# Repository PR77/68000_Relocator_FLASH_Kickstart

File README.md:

# 68000 Relocator with FLASH based Kickstart
Forked from https://github.com/AwesomeInferno/68000Relocator and modified to support FLASH Kickstart allowing programming in system.

# Warning
This design has not been compliance tested and will not be. It may cause damage to your A500. I take no responsibility for this. I accept no responsibility for any damage to any equipment that results from the use of this design and its components. IT IS ENTIRELY AT YOUR OWN RISK!

# Overview
To allow for Flash Kickstart images to be mapped in the same address space as existing ROM Kickstart without the need to remove the existing ROM. This design is targeting an accelerated A500(+) system which also require a CPU relocation.

### Appearance
Nice 3D model:

... this is the final design.

### Prototype
Drawing in from the experience and usefulness of my prototyping jig created for my Rev-1 Accelerator (https://github.com/PR77/A500_ACCEL_RAM_IDE-Rev-1), I decided to do the same for this hardware expansion.

So the prototype looks like this:

To keep the prototype simple, instead of using Flash devices (AMD AM29F040B are my target has I have these and experience with the devices) I used simple SRAMs (also from my Accelerator). There was also the learning curve with using VBCC (http://eab.abime.net/showthread.php?t=83113) to develop the software to control the hardware, but with that sorted out I managed to finally get the prototype to work.

### Final Hardware
Here is the final hardware loaded and installed with my Rev-2 Accelerator (https://github.com/PR77/A500_ACCEL_RAM_IDE-Rev-2). I was not able to easily source new AMD AM29F040B Flash devices so I changed over to SST39SF0x0A devices. They are JEDEC compliant so no issue with the pinout. Just watch out for the device identification in the SW.

### BOM
For those wanting to build their own hardware, here is the BOM;

| Reference(s) | Value      | Footprint                                                      |
|--------------|------------|----------------------------------------------------------------|
| C1           | 10uF       | Capacitors_Tantalum_SMD:CP_Tantalum_Case-B_EIA-3528-21_Hand    |
| C2           | 10uF       | Capacitors_Tantalum_SMD:CP_Tantalum_Case-B_EIA-3528-21_Hand    |
| C3           | 100nF      | Capacitors_SMD:C_0805_HandSoldering                            |
| C4           | 100nF      | Capacitors_SMD:C_0805_HandSoldering                            |
| C5           | 100nF      | Capacitors_SMD:C_0805_HandSoldering                            |
| C6           | 100nF      | Capacitors_SMD:C_0805_HandSoldering                            |
| J3           | BLOCK      | Pin_Headers:Pin_Header_Straight_1x02_Pitch2.54mm               |
| J4           | JTAG       | Pin_Headers:Pin_Header_Straight_1x06_Pitch2.54mm               |
| R1           | 10K        | Resistors_SMD:R_0805_HandSoldering                             |
| R2           | 10K        | Resistors_SMD:R_0805_HandSoldering                             |
| R3           | 10K        | Resistors_SMD:R_0805_HandSoldering                             |
| U1           | 68000D     | Pin_Headers:Pin_Header_Straight_2x32_Pitch2.54mm               |
| U2           | 68000D     | Housings_DIP:DIP-64_W22.86mm_Socket_LongPads                   |
| U3           | SST39SF040 | Housings_DIP:DIP-32_W15.24mm_Socket                            |
| U4           | SST39SF040 | Housings_DIP:DIP-32_W15.24mm_Socket                            |
| U5           | XC9572VQ44 | Housings_QFP:TQFP-44_10x10mm_Pitch0.8mm                        |
| U6           | LM1117-3.3 | TO_SOT_Packages_SMD:SOT-223-3_TabPin2                          |

### In Operation
My test Amiga 500 has a ROM Kickstart version 1.2, so the boot screen looks like this:

Then when loading into RAM Kickstart version 3.1 the software will make a simple dump of the RAM to the console to ensure it has been written correctly (data blurred to avoid any potential (C) issues). Essentially some basic debugging which looks like this:

... so now, using the magic sequence, I have Kickstart version 3.1 as shown here:

### How It Works
In principle the operation is fairly simple. A CPLD is used to switch between the ROM Kickstart on the Motherboard or the Flash Kickstart on the CPU Relocator. Switching is performed by an active /RESET (CTRL-A-A) without interruption for longer than 1 second. Shorter /RESET durations will simply just reset the Amiga. After a POR (Power On Reset) by default the Flash Kickstart on the CPU Relocator will be used.

#### ROM based Kickstart
When ROM Kickstart is being used, the hardware simply passed /AS to the Amiga Motherboard to allow GARY perform the address decode and chip select of the internal ROM. During this process, the Flash Kickstart is simply not used - except when programming. A Zorro II space of 512K is  requested and allocated by the Amiga which maps to the Flash devices.

When programming the Flash devices, access is via this Zorro II space. Programming of the Flash devices can only be performed when ROM Kickstart is being used.

#### FLASH based Kickstart
When Flash Kickstart is being used, the hardware simply blocks /AS to the Amiga Motherboard and the CPLD will perform the operation of Flash device control. As /AS is not asserted on the Amiga Motherboard, and therefore no GARY decode, the Relocator CPLD will then also assert the /DTACK after placing data on the bus - this is needed to complete the CPU cycle.

Flash Kickstarts will always be visible from base address 0xF80000. This means, if 256K images would be used, then it will need to be duplicated to populate the entire 512K region size. This is to ensure the correct SP and IP initisation (see Overlay Interception). 256K images generally start from address 0xFC0000 (as opposed to 0xF80000).

#### Overlay Interception
When Flash Kickstart mode is being used, the CPLD will also intercept the overlay of the Kickstart in the 0x000000 memory space until the first access to the custom chip register is performed. This ensures the correct SP and IP initialisation is performed directly after POR (Power On Reset) as the Flash Kickstart is used by default.

### Known Issues And Pending Items
The following items are pending:

1. Will update the software to not load the entire Kickstart content into RAM before programming; rather will load 64K chunks at a time.
2. Support for ROMs based at address 0xF00000.

### External Contributions
Thanks to the Open Source efforts, here is a list of improvements people have made:

1. Side Slot expander version and GUI - https://github.com/KaiEmilW/A500-Side-Expansion-Slot-CPU-Relocator

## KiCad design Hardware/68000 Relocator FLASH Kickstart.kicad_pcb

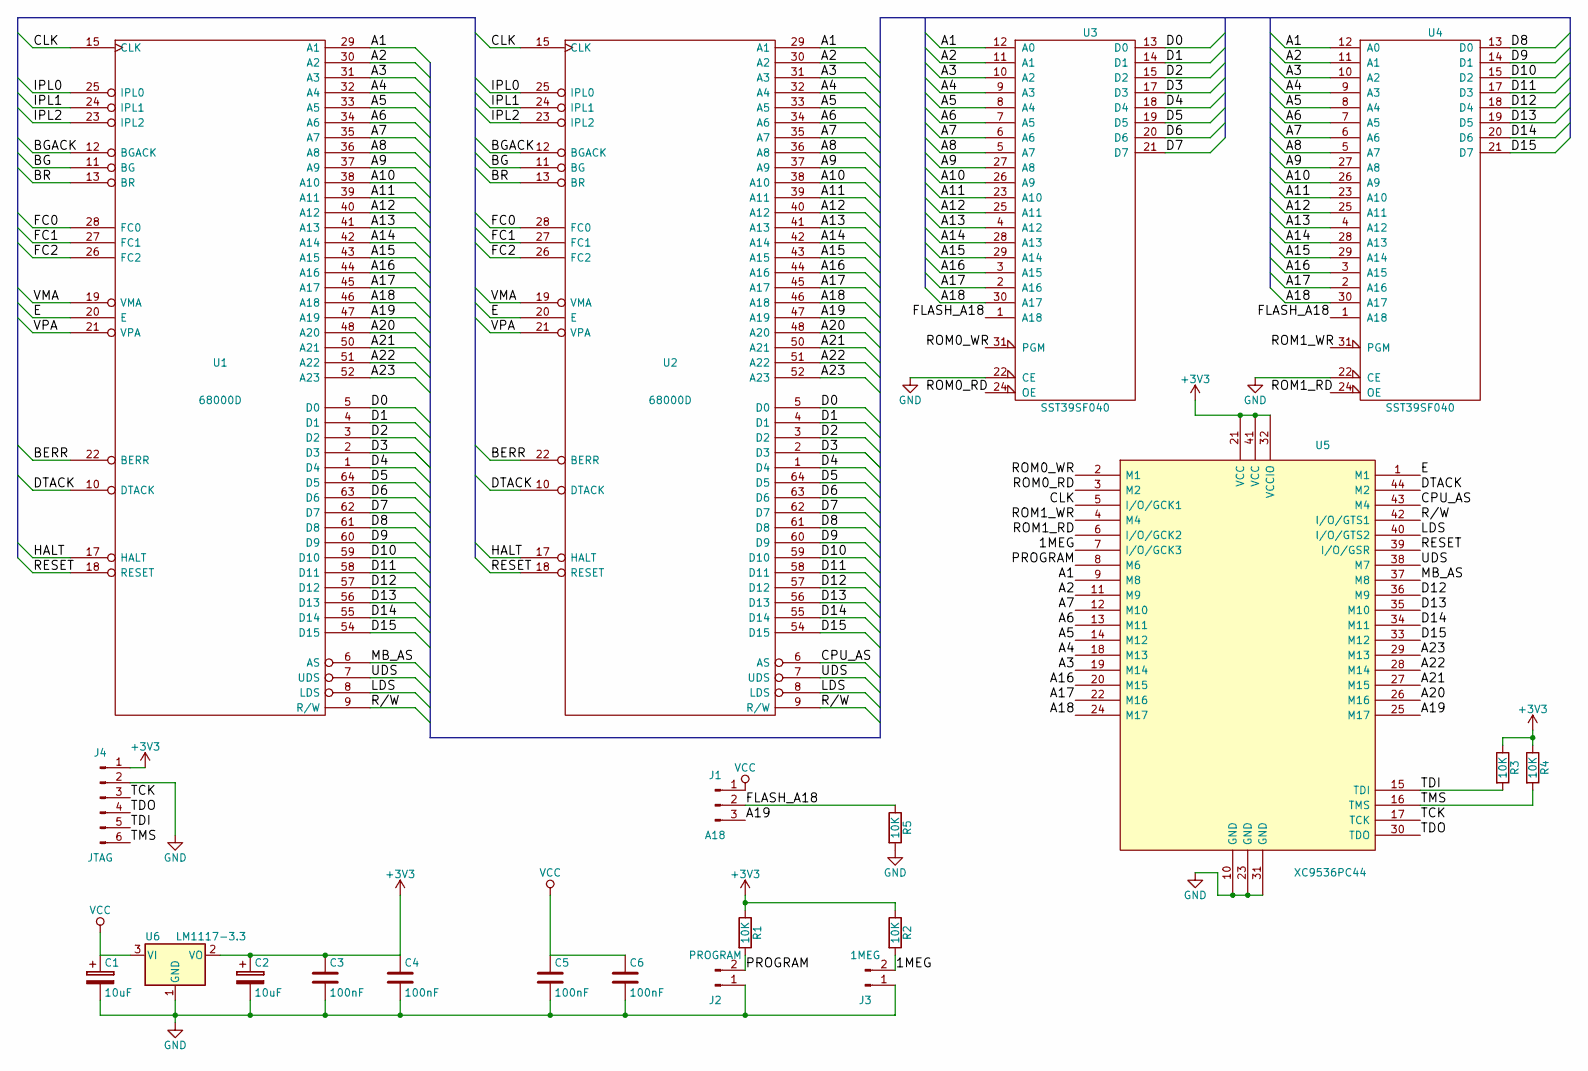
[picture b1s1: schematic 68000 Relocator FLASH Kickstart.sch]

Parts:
C1, C2: 10uF; CP_Tantalum_Case-B_EIA-3528-21_Hand
C3, C4, C5, C6: 100nF; C_0805_HandSoldering
J1: A18; Pin_Header_Straight_1x03_Pitch2.54mm
J2: PROGRAM; Pin_Header_Straight_1x02_Pitch2.54mm
J3: 1MEG; Pin_Header_Straight_1x02_Pitch2.54mm
J4: JTAG; Pin_Header_Straight_1x06_Pitch2.54mm
R1, R2, R3, R4, R5: 10K; R_0805_HandSoldering
U1, U2: 68000D; DIP-64_W22.86mm_Socket_LongPads
U3, U4: SST39SF040; PLCC-32
U5: XC9536PC44; TQFP-44_10x10mm_Pitch0.8mm
U6: LM1117-3.3; SOT-223-3_TabPin2

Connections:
+3V3: C2.1, C3.1, C4.1, J4.1, R1.1, R2.1, R3.1, R4.1, U5.21 (VCC), U5.32 (VCCIO), U5.41 (VCC), U6.2 (VO)
/1MEG: J3.2, R2.2, U5.7 (I/O/GCK3)
/A1: U1.29 (A1), U2.29 (A1), U3.12 (A0), U4.12 (A0), U5.9 (M8)
/A2: U1.30 (A2), U2.30 (A2), U3.11 (A1), U4.11 (A1), U5.11 (M9)
/A3: U1.31 (A3), U2.31 (A3), U3.10 (A2), U4.10 (A2), U5.19 (M14)
/A4: U1.32 (A4), U2.32 (A4), U3.9 (A3), U4.9 (A3), U5.18 (M13)
/A5: U1.33 (A5), U2.33 (A5), U3.8 (A4), U4.8 (A4), U5.14 (M12)
/A6: U1.34 (A6), U2.34 (A6), U3.7 (A5), U4.7 (A5), U5.13 (M11)
/A7: U1.35 (A7), U2.35 (A7), U3.6 (A6), U4.6 (A6), U5.12 (M10)
/A8: U1.36 (A8), U2.36 (A8), U3.5 (A7), U4.5 (A7)
/A9: U1.37 (A9), U2.37 (A9), U3.27 (A8), U4.27 (A8)
/A10: U1.38 (A10), U2.38 (A10), U3.26 (A9), U4.26 (A9)
/A11: U1.39 (A11), U2.39 (A11), U3.23 (A10), U4.23 (A10)
/A12: U1.40 (A12), U2.40 (A12), U3.25 (A11), U4.25 (A11)
/A13: U1.41 (A13), U2.41 (A13), U3.4 (A12), U4.4 (A12)
/A14: U1.42 (A14), U2.42 (A14), U3.28 (A13), U4.28 (A13)
/A15: U1.43 (A15), U2.43 (A15), U3.29 (A14), U4.29 (A14)
/A16: U1.44 (A16), U2.44 (A16), U3.3 (A15), U4.3 (A15), U5.20 (M15)
/A17: U1.45 (A17), U2.45 (A17), U3.2 (A16), U4.2 (A16), U5.22 (M16)
/A18: U1.46 (A18), U2.46 (A18), U3.30 (A17), U4.30 (A17), U5.24 (M17)
/A19: J1.3, U1.47 (A19), U2.47 (A19), U5.25 (M17)
/A20: U1.48 (A20), U2.48 (A20), U5.26 (M16)
/A21: U1.50 (A21), U2.50 (A21), U5.27 (M15)
/A22: U1.51 (A22), U2.51 (A22), U5.28 (M14)
/A23: U1.52 (A23), U2.52 (A23), U5.29 (M13)
/BERR: U1.22 (BERR), U2.22 (BERR)
/BG: U1.11 (BG), U2.11 (BG)
/BGACK: U1.12 (BGACK), U2.12 (BGACK)
/BR: U1.13 (BR), U2.13 (BR)
/CLK: U1.15 (CLK), U2.15 (CLK), U5.5 (I/O/GCK1)
/CPU_AS: U2.6 (AS), U5.43 (M4)
/D0: U1.5 (D0), U2.5 (D0), U3.13 (D0)
/D1: U1.4 (D1), U2.4 (D1), U3.14 (D1)
/D2: U1.3 (D2), U2.3 (D2), U3.15 (D2)
/D3: U1.2 (D3), U2.2 (D3), U3.17 (D3)
/D4: U1.1 (D4), U2.1 (D4), U3.18 (D4)
/D5: U1.64 (D5), U2.64 (D5), U3.19 (D5)
/D6: U1.63 (D6), U2.63 (D6), U3.20 (D6)
/D7: U1.62 (D7), U2.62 (D7), U3.21 (D7)
/D8: U1.61 (D8), U2.61 (D8), U4.13 (D0)
/D9: U1.60 (D9), U2.60 (D9), U4.14 (D1)
/D10: U1.59 (D10), U2.59 (D10), U4.15 (D2)
/D11: U1.58 (D11), U2.58 (D11), U4.17 (D3)
/D12: U1.57 (D12), U2.57 (D12), U4.18 (D4), U5.36 (M9)
/D13: U1.56 (D13), U2.56 (D13), U4.19 (D5), U5.35 (M10)
/D14: U1.55 (D14), U2.55 (D14), U4.20 (D6), U5.34 (M11)
/D15: U1.54 (D15), U2.54 (D15), U4.21 (D7), U5.33 (M12)
/DTACK: U1.10 (DTACK), U2.10 (DTACK), U5.44 (M2)
/E: U1.20 (E), U2.20 (E), U5.1 (M1)
/FC0: U1.28 (FC0), U2.28 (FC0)
/FC1: U1.27 (FC1), U2.27 (FC1)
/FC2: U1.26 (FC2), U2.26 (FC2)
/FLASH_A18: J1.2, R5.1, U3.1 (A18), U4.1 (A18)
/HALT: U1.17 (HALT), U2.17 (HALT)
/IPL0: U1.25 (IPL0), U2.25 (IPL0)
/IPL1: U1.24 (IPL1), U2.24 (IPL1)
/IPL2: U1.23 (IPL2), U2.23 (IPL2)
/LDS: U1.8 (LDS), U2.8 (LDS), U5.40 (I/O/GTS2)
/MB_AS: U1.6 (AS), U5.37 (M8)
/PROGRAM: J2.2, R1.2, U5.8 (M6)
/R/W: U1.9 (R/W), U2.9 (R/W), U5.42 (I/O/GTS1)
/RESET: U1.18 (RESET), U2.18 (RESET), U5.39 (I/O/GSR)
/ROM0_RD: U5.3 (M2)
/ROM0_WR: U5.2 (M1)
/ROM1_RD: U5.6 (I/O/GCK2)
/ROM1_WR: U5.4 (M4)
/TCK: J4.3, U5.17 (TCK)
/TDI: J4.5, R3.2, U5.15 (TDI)
/TDO: J4.4, U5.30 (TDO)
/TMS: J4.6, R4.2, U5.16 (TMS)
/UDS: U1.7 (UDS), U2.7 (UDS), U5.38 (M7)
/VMA: U1.19 (VMA), U2.19 (VMA)
/VPA: U1.21 (VPA), U2.21 (VPA)
GND: C1.2, C2.2, C3.2, C4.2, C5.2, C6.2, J2.1, J3.1, J4.2, R5.2, U1.16 (GND), U1.53 (GND), U2.16 (GND), U2.53 (GND), U3.16 (GND), U3.22 (CE), U4.16 (GND), U4.22 (CE), U5.10 (GND), U5.23 (GND), U5.31 (GND), U6.1 (GND)
VCC: C1.1, C5.1, C6.1, J1.1, U1.14 (VCC), U1.49 (VCC), U2.14 (VCC), U2.49 (VCC), U3.32 (VCC), U4.32 (VCC), U6.3 (VI)

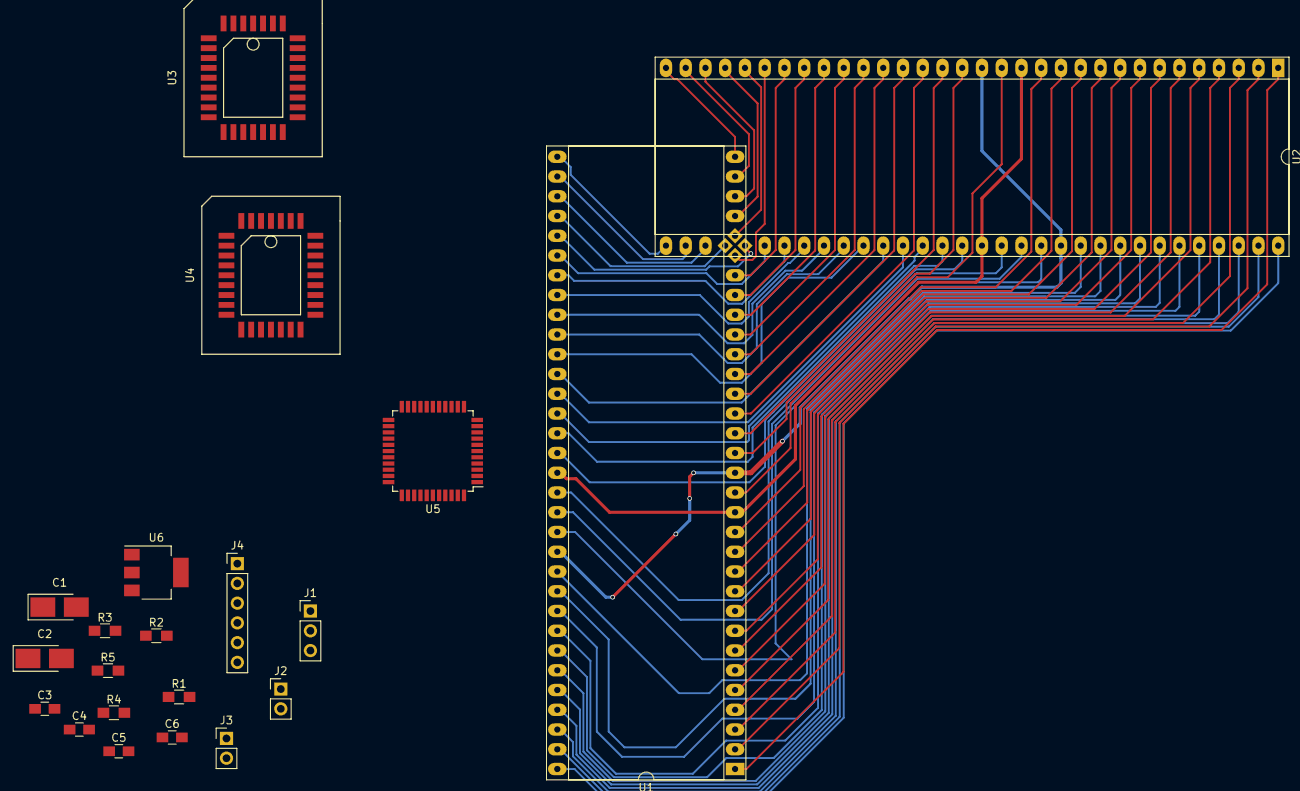
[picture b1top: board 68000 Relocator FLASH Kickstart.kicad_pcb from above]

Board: 2 copper layers, 21 parts (0 on the bottom side), 71 nets.

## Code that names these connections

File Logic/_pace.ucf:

#PACE: Start of Constraints generated by PACE

#PACE: Start of PACE I/O Pin Assignments
NET "ADDRESS_HIGH<16>"  LOC = "P8"  ;
NET "ADDRESS_HIGH<17>"  LOC = "P7"  ;
NET "ADDRESS_HIGH<18>"  LOC = "P6"  ;
NET "ADDRESS_HIGH<19>"  LOC = "P5"  ;
NET "ADDRESS_HIGH<20>"  LOC = "P4"  ;
NET "ADDRESS_HIGH<21>"  LOC = "P3"  ;
NET "ADDRESS_HIGH<22>"  LOC = "P2"  ;
NET "ADDRESS_HIGH<23>"  LOC = "P1"  ;
NET "ADDRESS_LOW<0>"  LOC = "P25"  ;
NET "ADDRESS_LOW<1>"  LOC = "P24"  ;
NET "ADDRESS_LOW<2>"  LOC = "P20"  ;
NET "ADDRESS_LOW<3>"  LOC = "P19"  ;
NET "ADDRESS_LOW<4>"  LOC = "P13"  ;
NET "ADDRESS_LOW<5>"  LOC = "P11"  ;
NET "ADDRESS_LOW<6>"  LOC = "P9"  ;
NET "CPU_AS"  LOC = "P34"  ; 
NET "CPU_E"  LOC = "P26"  ;
NET "DATA<12>"  LOC = "P18"  ; 
NET "DATA<14>"  LOC = "P14"  ; 
NET "DATA<15>"  LOC = "P12"  ; 
NET "FLASH_RD<0>"  LOC = "P37"  ;
NET "FLASH_RD<1>"  LOC = "P36"  ;
NET "FLASH_WR<0>"  LOC = "P28"  ;
NET "FLASH_WR<1>"  LOC = "P27"  ;
NET "MB_AS"  LOC = "P35"  ; 
NET "MB_CLK"  LOC = "P22"  ; 
NET "MB_DTACK"  LOC = "P29"  ; 
NET "PROGRAM"  LOC = "P38"  ;
NET "UDS"  LOC = "P33"  ; 

#PACE: Start of PACE Area Constraints

#PACE: Start of PACE Prohibit Constraints

#PACE: End of Constraints generated by PACE

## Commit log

2018-10-20 Updates
    Compiles but does not link
2018-10-23 Updates with more debugging
2018-10-29 Updates. More debugging
2019-01-09 Updates
    Working with prototype hardware.
2019-05-05 Updates
    Finalised PCB layout.
2019-05-06 Updates
    Fixed bottom solder mask.
2019-05-22 Updates
    Add BOM.
2019-05-22 Updates
    Removed Datasheet from BOM listing.
2019-05-27 Updates
    Added a verify function and addressed a nasty bug in checkFlashStatus().
2019-06-12 Rewrote Verilog code to hopefully fix glitches. Needs testing.
2019-06-12 Updates
    Rewrote Verilog to address cascaded Autoconfig glitch.
2019-06-13 Updates
    Added JED output and cleaned up XISE Project file.
2020-08-22 Updates
    Refactored and issues corrected.
2020-12-26 Updates and cleanups
    First pass of updates / cleanups to this tree.
    * The Hardware was in a zip file which made it difficult to make
    modifications, this is now stored as individual files.
    * The Verilog has been modified so that motherboard ROM booting is
    default.
    * The jed file has been updated based on previous bug fixes and the
2020-12-26 Version 2.0 of FlashKickstart executable
    * Minor code cleanup
    * Switch to gcc cross-compile
    * Erase ROM before flashing
    * Add Kickstart version identification for motherboard, flash and file
2020-12-27 FlashKickstart 2.1
    Has the following changes:
    * Added basic JEDEC device identification
    * More user friendly output
    * Removed TEST option
    * Added warning for byte swapped
    * Added DiagROM identification
2020-12-28 Multi-ROM support
    When 1MB of flash is fitted you can load two ROMs into flash. The reset
    switching will switch between motherboard, lo ROM and hi ROM in a cycle.
    Defaulting to the motherboard ROM.
2020-12-29 Software cleanups
    * Fix compiler warnings / bugs
    * Fix location of 256K ROMs
    * Show if ROM is erased
    * Change to ROM 1/2 instead of hi/lo (to avoid confusion with hi/lo
    bytes for the real ROMs)
    * Fix detection for a few different KS versions
2021-02-13 Initial commit of GUI v1.0
2021-02-14 Updates
    Added GitHub Reference to Fk executable and updated JED.
2021-03-09 Fix the sector erase maths
    SST39 has 4KB sectors to erase, so some of the maths is a bit off.
2021-05-16 Updates
    Additional details to "Flash based Kickstart" when using 256K image sizes.
2023-01-20 Updated Gerbers
2023-01-20 Removed redundant ZIP file
2025-11-24 Updates
    Fixed a bug that would result in write errors sometimes.
2025-11-26 Updates
    Simple updates and added retry strategy if write fails.
2025-11-27 Updates
    Updates to Verilog. Minor formatting improvements and added some necessary comments to the verilog. Qualified DTACK_n with LDS_n and UDS_n signals.
2025-11-27 Updates
    Removed superfluous files.
